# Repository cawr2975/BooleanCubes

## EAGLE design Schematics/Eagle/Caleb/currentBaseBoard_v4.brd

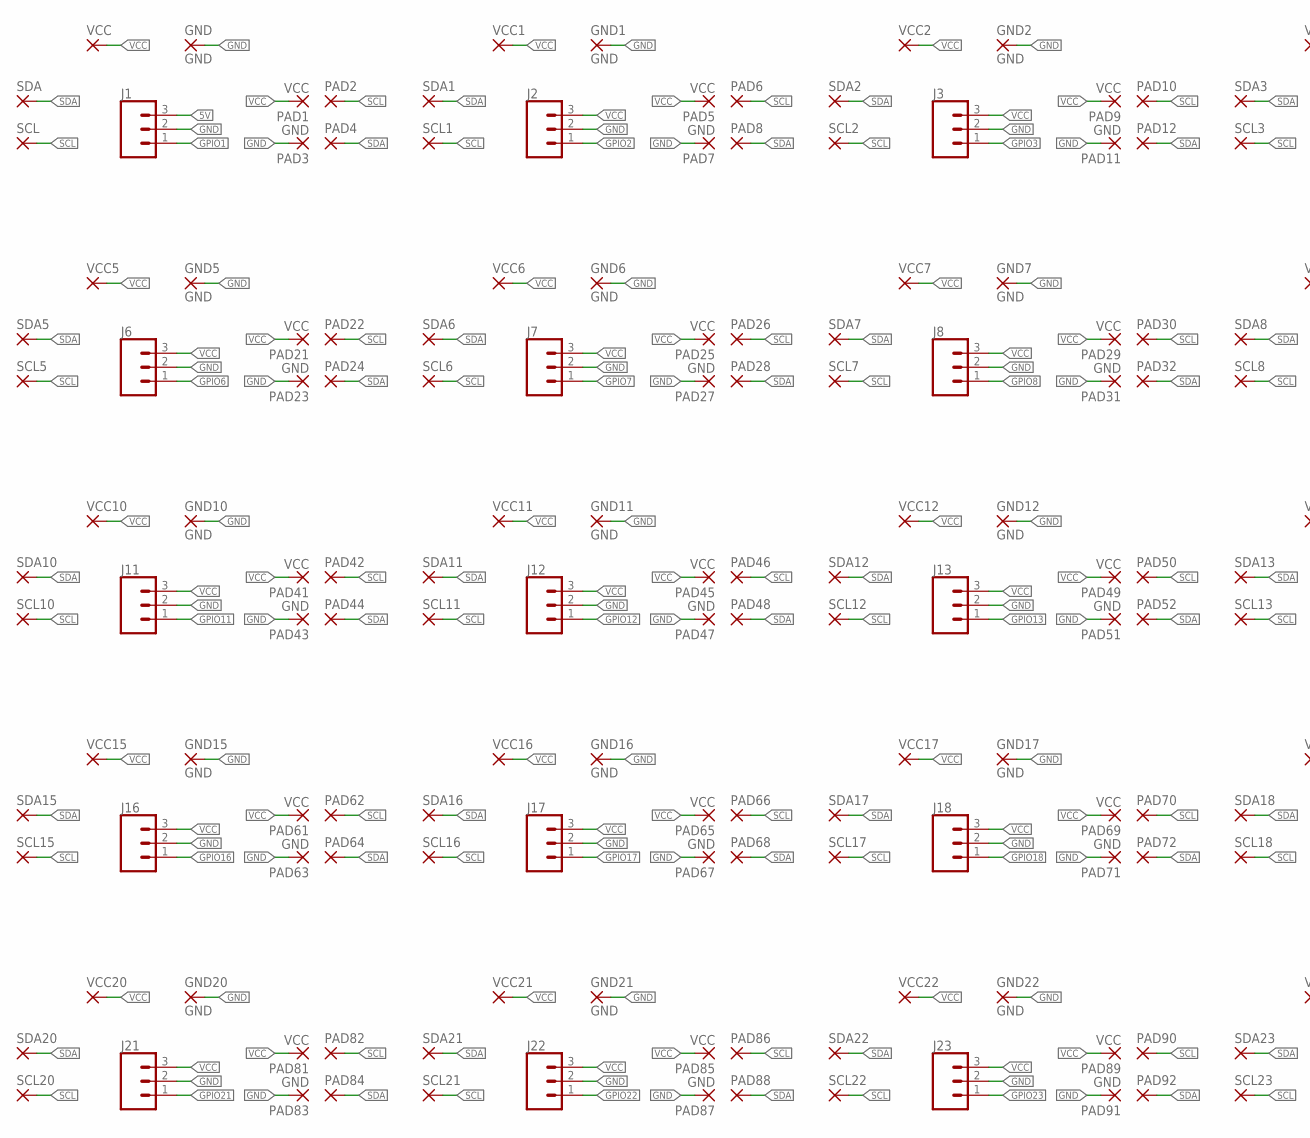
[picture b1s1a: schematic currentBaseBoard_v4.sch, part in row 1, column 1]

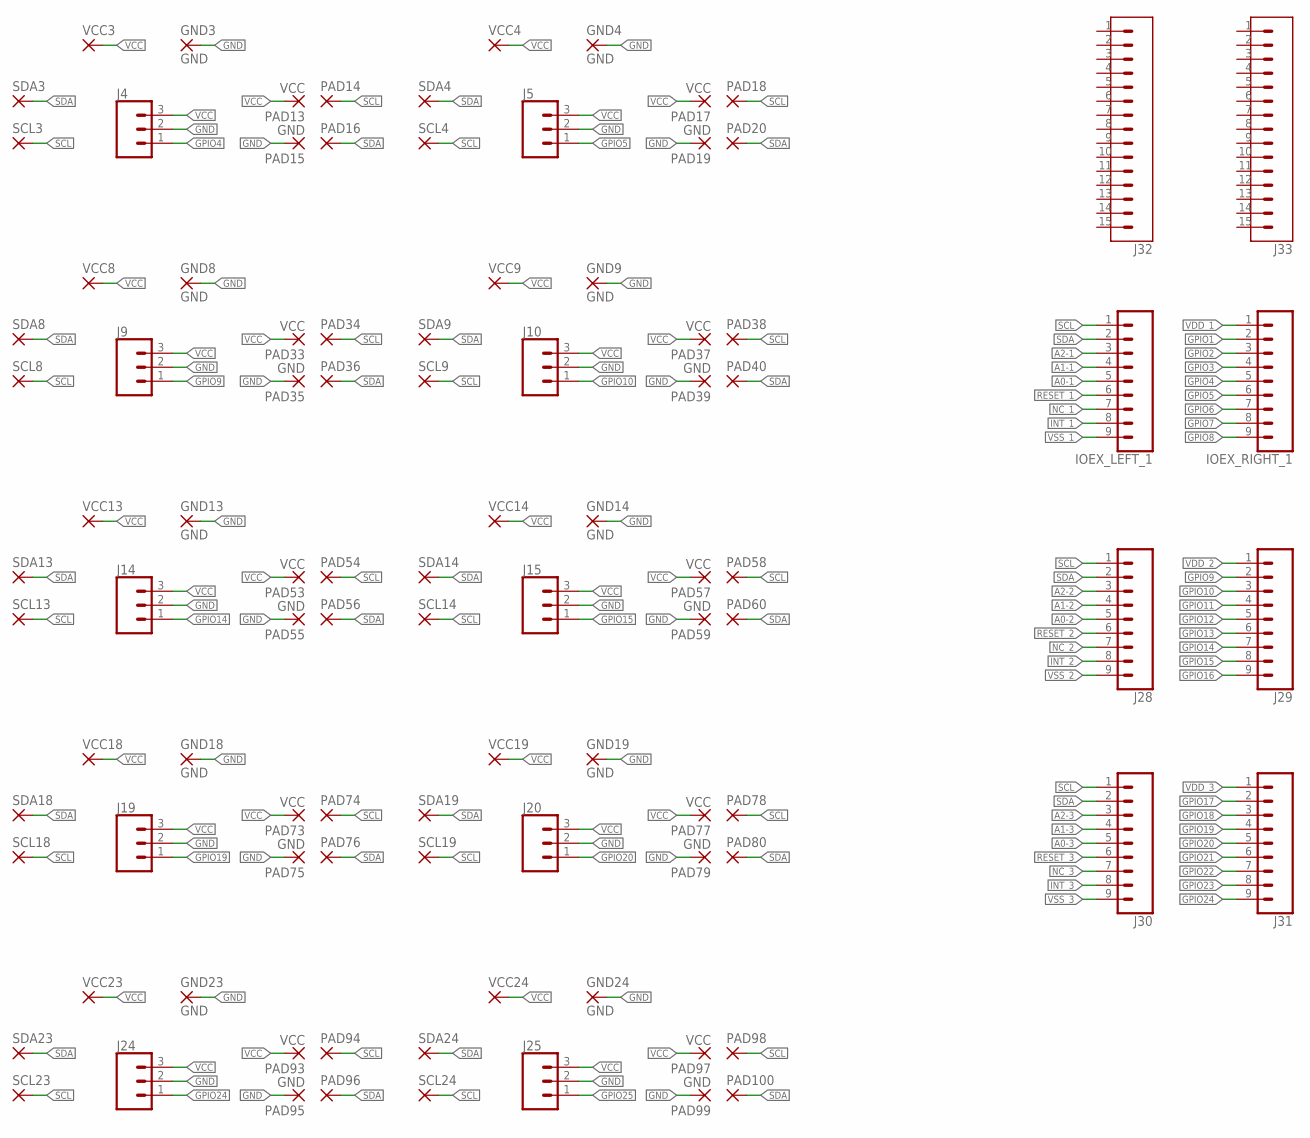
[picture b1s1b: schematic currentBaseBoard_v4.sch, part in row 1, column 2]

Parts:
GND, GND1, GND2, GND3, GND4, GND5, GND6, GND7, GND8, GND9, GND10, GND11, GND12, GND13, GND14, GND15, GND16, GND17, GND18, GND19, GND20, GND21, GND22, GND23, GND24: GND; 2,15/1,0
IOEX_LEFT_1: CONN_09; 1X09
IOEX_RIGHT_1: CONN_09; 1X09
J1, J2, J3, J4, J5, J6, J7, J8, J9, J10, J11, J12, J13, J14, J15, J16, J17, J18, J19, J20, J21, J22, J23, J24, J25: CONN_03; 1X03
J28, J29, J30, J31: CONN_09; 1X09
J32, J33: CONN_06SMD_MALE; 1X15_SMD_MALE
PAD1, PAD5, PAD9, PAD13, PAD17, PAD21, PAD25, PAD29, PAD33, PAD37, PAD41, PAD45, PAD49, PAD53, PAD57, PAD61, PAD65, PAD69, PAD73, PAD77, PAD81, PAD85, PAD89, PAD93, PAD97: VCC; 2,15/1,0
PAD2, PAD4, PAD6, PAD8, PAD10, PAD12, PAD14, PAD16, PAD18, PAD20, PAD22, PAD24, PAD26, PAD28, PAD30, PAD32, PAD34, PAD36, PAD38, PAD40, PAD42, PAD44, PAD46, PAD48, PAD50, PAD52, PAD54, PAD56, PAD58, PAD60, PAD62, PAD64, PAD66, PAD68, PAD70, PAD72, PAD74, PAD76, PAD78, PAD80, PAD82, PAD84, PAD86, PAD88, PAD90, PAD92, PAD94, PAD96, PAD98, PAD100: 2,15/1,0
PAD3, PAD7, PAD11, PAD15, PAD19, PAD23, PAD27, PAD31, PAD35, PAD39, PAD43, PAD47, PAD51, PAD55, PAD59, PAD63, PAD67, PAD71, PAD75, PAD79, PAD83, PAD87, PAD91, PAD95, PAD99: GND; 2,15/1,0
SCL, SCL1, SCL2, SCL3, SCL4, SCL5, SCL6, SCL7, SCL8, SCL9, SCL10, SCL11, SCL12, SCL13, SCL14, SCL15, SCL16, SCL17, SCL18, SCL19, SCL20, SCL21, SCL22, SCL23, SCL24: 2,15/1,0
SDA, SDA1, SDA2, SDA3, SDA4, SDA5, SDA6, SDA7, SDA8, SDA9, SDA10, SDA11, SDA12, SDA13, SDA14, SDA15, SDA16, SDA17, SDA18, SDA19, SDA20, SDA21, SDA22, SDA23, SDA24: 2,15/1,0
VCC, VCC1, VCC2, VCC3, VCC4, VCC5, VCC6, VCC7, VCC8, VCC9, VCC10, VCC11, VCC12, VCC13, VCC14, VCC15, VCC16, VCC17, VCC18, VCC19, VCC20, VCC21, VCC22, VCC23, VCC24: 2,15/1,0

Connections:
5V: J1.3
A0-1: IOEX_LEFT_1.5
A0-2: J28.5
A0-3: J30.5
A1-1: IOEX_LEFT_1.4
A1-2: J28.4
A1-3: J30.4
A2-1: IOEX_LEFT_1.3
A2-2: J28.3
A2-3: J30.3
GND: GND.1, GND1.1, GND2.1, GND3.1, GND4.1, GND5.1, GND6.1, GND7.1, GND8.1, GND9.1, GND10.1, GND11.1, GND12.1, GND13.1, GND14.1, GND15.1, GND16.1, GND17.1, GND18.1, GND19.1, GND20.1, GND21.1, GND22.1, GND23.1, GND24.1, J1.2, J2.2, J3.2, J4.2, J5.2, J6.2, J7.2, J8.2, J9.2, J10.2, J11.2, J12.2, J13.2, J14.2, J15.2, J16.2, J17.2, J18.2, J19.2, J20.2, J21.2, J22.2, J23.2, J24.2, J25.2, PAD3.1, PAD7.1, PAD11.1, PAD15.1, PAD19.1, PAD23.1, PAD27.1, PAD31.1, PAD35.1, PAD39.1, PAD43.1, PAD47.1, PAD51.1, PAD55.1, PAD59.1, PAD63.1, PAD67.1, PAD71.1, PAD75.1, PAD79.1, PAD83.1, PAD87.1, PAD91.1, PAD95.1, PAD99.1
GPIO1: IOEX_RIGHT_1.2, J1.1
GPIO2: IOEX_RIGHT_1.3, J2.1
GPIO3: IOEX_RIGHT_1.4, J3.1
GPIO4: IOEX_RIGHT_1.5, J4.1
GPIO5: IOEX_RIGHT_1.6, J5.1
GPIO6: IOEX_RIGHT_1.7, J6.1
GPIO7: IOEX_RIGHT_1.8, J7.1
GPIO8: IOEX_RIGHT_1.9, J8.1
GPIO9: J9.1, J29.2
GPIO10: J10.1, J29.3
GPIO11: J11.1, J29.4
GPIO12: J12.1, J29.5
GPIO13: J13.1, J29.6
GPIO14: J14.1, J29.7
GPIO15: J15.1, J29.8
GPIO16: J16.1, J29.9
GPIO17: J17.1, J31.2
GPIO18: J18.1, J31.3
GPIO19: J19.1, J31.4
GPIO20: J20.1, J31.5
GPIO21: J21.1, J31.6
GPIO22: J22.1, J31.7
GPIO23: J23.1, J31.8
GPIO24: J24.1, J31.9
GPIO25: J25.1
INT_1: IOEX_LEFT_1.8
INT_2: J28.8
INT_3: J30.8
NC_1: IOEX_LEFT_1.7
NC_2: J28.7
NC_3: J30.7
RESET_1: IOEX_LEFT_1.6
RESET_2: J28.6
RESET_3: J30.6
SCL: IOEX_LEFT_1.1, J28.1, J30.1, PAD2.1, PAD6.1, PAD10.1, PAD14.1, PAD18.1, PAD22.1, PAD26.1, PAD30.1, PAD34.1, PAD38.1, PAD42.1, PAD46.1, PAD50.1, PAD54.1, PAD58.1, PAD62.1, PAD66.1, PAD70.1, PAD74.1, PAD78.1, PAD82.1, PAD86.1, PAD90.1, PAD94.1, PAD98.1, SCL.1, SCL1.1, SCL2.1, SCL3.1, SCL4.1, SCL5.1, SCL6.1, SCL7.1, SCL8.1, SCL9.1, SCL10.1, SCL11.1, SCL12.1, SCL13.1, SCL14.1, SCL15.1, SCL16.1, SCL17.1, SCL18.1, SCL19.1, SCL20.1, SCL21.1, SCL22.1, SCL23.1, SCL24.1
SDA: IOEX_LEFT_1.2, J28.2, J30.2, PAD4.1, PAD8.1, PAD12.1, PAD16.1, PAD20.1, PAD24.1, PAD28.1, PAD32.1, PAD36.1, PAD40.1, PAD44.1, PAD48.1, PAD52.1, PAD56.1, PAD60.1, PAD64.1, PAD68.1, PAD72.1, PAD76.1, PAD80.1, PAD84.1, PAD88.1, PAD92.1, PAD96.1, PAD100.1, SDA.1, SDA1.1, SDA2.1, SDA3.1, SDA4.1, SDA5.1, SDA6.1, SDA7.1, SDA8.1, SDA9.1, SDA10.1, SDA11.1, SDA12.1, SDA13.1, SDA14.1, SDA15.1, SDA16.1, SDA17.1, SDA18.1, SDA19.1, SDA20.1, SDA21.1, SDA22.1, SDA23.1, SDA24.1
VCC: J2.3, J3.3, J4.3, J5.3, J6.3, J7.3, J8.3, J9.3, J10.3, J11.3, J12.3, J13.3, J14.3, J15.3, J16.3, J17.3, J18.3, J19.3, J20.3, J21.3, J22.3, J23.3, J24.3, J25.3, PAD1.1, PAD5.1, PAD9.1, PAD13.1, PAD17.1, PAD21.1, PAD25.1, PAD29.1, PAD33.1, PAD37.1, PAD41.1, PAD45.1, PAD49.1, PAD53.1, PAD57.1, PAD61.1, PAD65.1, PAD69.1, PAD73.1, PAD77.1, PAD81.1, PAD85.1, PAD89.1, PAD93.1, PAD97.1, VCC.1, VCC1.1, VCC2.1, VCC3.1, VCC4.1, VCC5.1, VCC6.1, VCC7.1, VCC8.1, VCC9.1, VCC10.1, VCC11.1, VCC12.1, VCC13.1, VCC14.1, VCC15.1, VCC16.1, VCC17.1, VCC18.1, VCC19.1, VCC20.1, VCC21.1, VCC22.1, VCC23.1, VCC24.1
VDD_1: IOEX_RIGHT_1.1
VDD_2: J29.1
VDD_3: J31.1
VSS_1: IOEX_LEFT_1.9
VSS_2: J28.9
VSS_3: J30.9

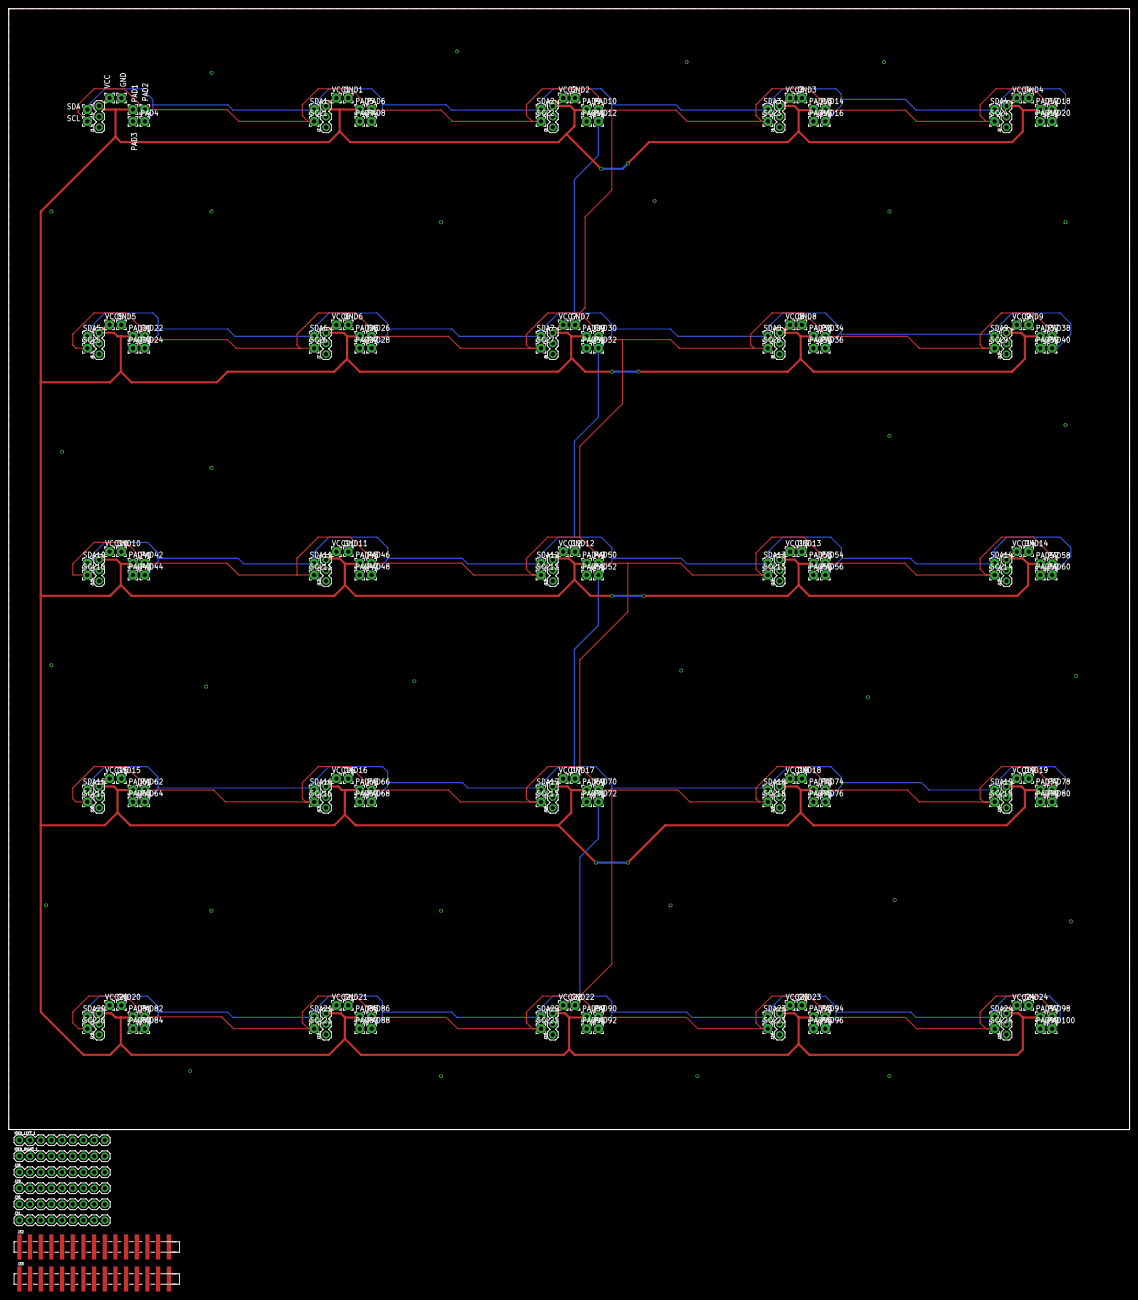
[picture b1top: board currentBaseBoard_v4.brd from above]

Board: 2 copper layers, 266.7 x 266.7 mm, 233 parts (0 on the bottom side), 28 nets.

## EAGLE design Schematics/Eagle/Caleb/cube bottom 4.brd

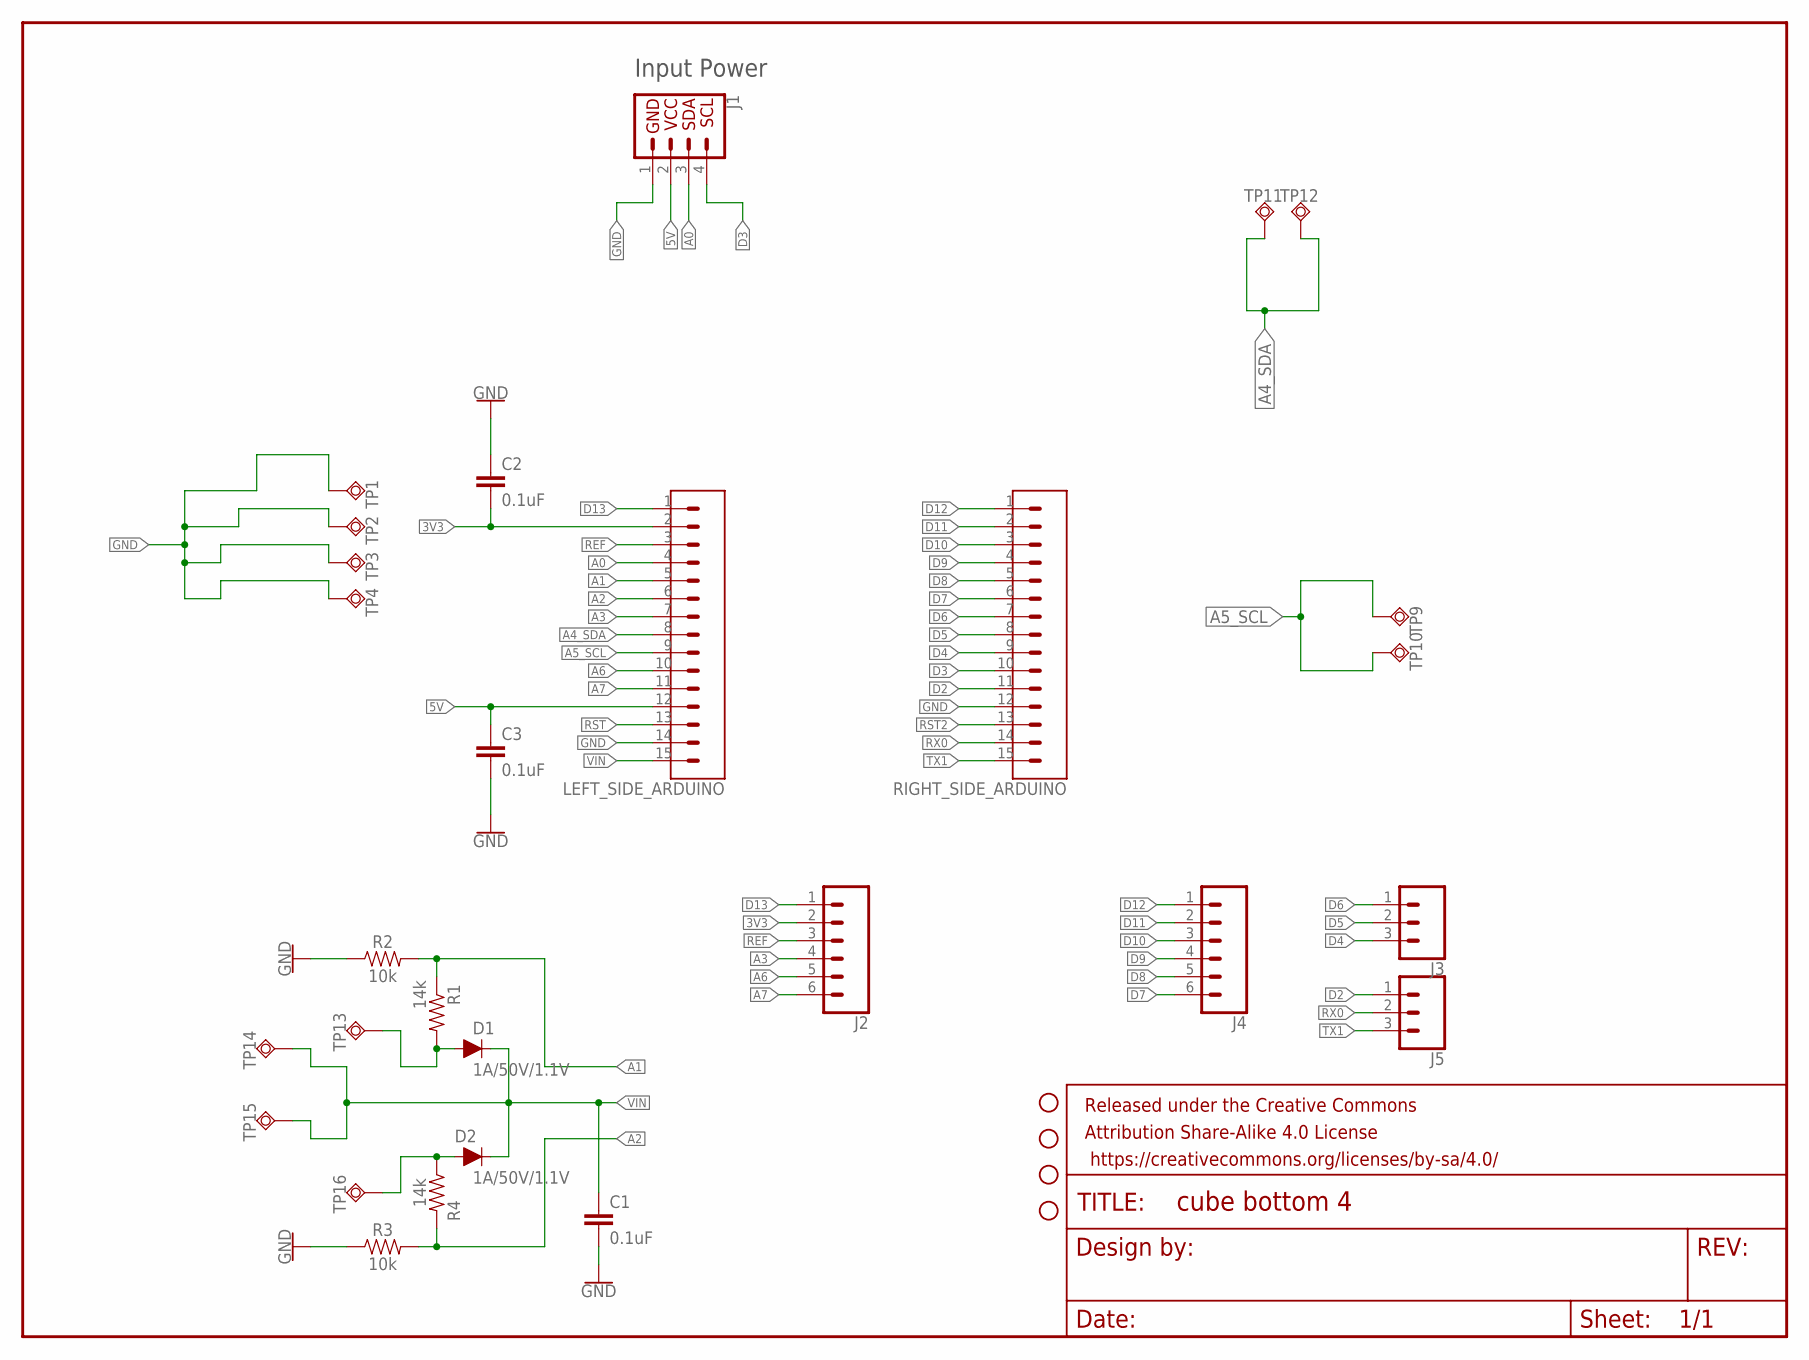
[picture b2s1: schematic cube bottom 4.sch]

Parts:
C1, C2, C3: 0.1uF; 0603
D1, D2: 1A/50V/1.1V; DIODE-1N4001
FRAME1: FRAME-LETTERNO_PACKAGE; DUMMY
H1, H2, H3, H4: STAND-OFF
J1: QWIIC_CONNECTORJS-1MM; 1X04_1MM_RA
J2, J4: CONN_06SILK_FEMALE_PTH; 1X06
J3, J5: CONN_03; 1X03
LEFT_SIDE_ARDUINO: CONN_06SMD_MALE; 1X15_SMD_MALE
R1, R4: 14k; 0603
R2, R3: 10k; 0603
RIGHT_SIDE_ARDUINO: CONN_06SMD_MALE; 1X15_SMD_MALE
TP1, TP2, TP3, TP4, TP9, TP10, TP11, TP12, TP13, TP14, TP15, TP16: TPSQTP20SQ; TP20SQ

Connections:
3V3: C2.2, J2.2, LEFT_SIDE_ARDUINO.2
5V: C3.1, J1.2 (VCC), LEFT_SIDE_ARDUINO.12
A0: J1.3 (SDA), LEFT_SIDE_ARDUINO.4
A1: LEFT_SIDE_ARDUINO.5, R1.1, R2.2
A2: LEFT_SIDE_ARDUINO.6, R3.2, R4.2
A3: J2.4, LEFT_SIDE_ARDUINO.7
A4_SDA: LEFT_SIDE_ARDUINO.8, TP11.TP, TP12.TP
A5_SCL: LEFT_SIDE_ARDUINO.9, TP9.TP, TP10.TP
A6: J2.5, LEFT_SIDE_ARDUINO.10
A7: J2.6, LEFT_SIDE_ARDUINO.11
D2: J5.1, RIGHT_SIDE_ARDUINO.11
D3: J1.4 (SCL), RIGHT_SIDE_ARDUINO.10
D4: J3.3, RIGHT_SIDE_ARDUINO.9
D5: J3.2, RIGHT_SIDE_ARDUINO.8
D6: J3.1, RIGHT_SIDE_ARDUINO.7
D7: J4.6, RIGHT_SIDE_ARDUINO.6
D8: J4.5, RIGHT_SIDE_ARDUINO.5
D9: J4.4, RIGHT_SIDE_ARDUINO.4
D10: J4.3, RIGHT_SIDE_ARDUINO.3
D11: J4.2, RIGHT_SIDE_ARDUINO.2
D12: J4.1, RIGHT_SIDE_ARDUINO.1
D13: J2.1, LEFT_SIDE_ARDUINO.1
DTP1: D2.A, R4.1, TP16.TP
DTP2: D1.A, R1.2, TP13.TP
GND: C1.2, C2.1, C3.2, J1.1 (GND), LEFT_SIDE_ARDUINO.14, R2.1, R3.1, RIGHT_SIDE_ARDUINO.12, TP1.TP, TP2.TP, TP3.TP, TP4.TP
REF: J2.3, LEFT_SIDE_ARDUINO.3
RST: LEFT_SIDE_ARDUINO.13
RST2: RIGHT_SIDE_ARDUINO.13
RX0: J5.2, RIGHT_SIDE_ARDUINO.14
TX1: J5.3, RIGHT_SIDE_ARDUINO.15
VIN: C1.1, D1.C, D2.C, LEFT_SIDE_ARDUINO.15, TP14.TP, TP15.TP

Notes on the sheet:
Input Power

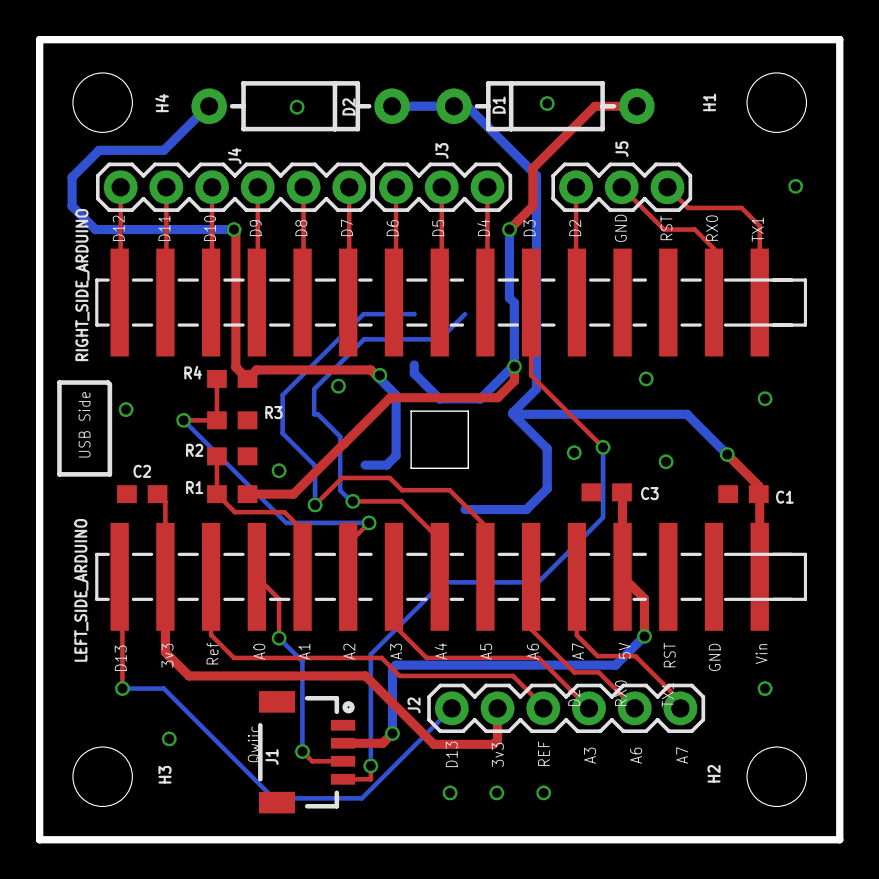
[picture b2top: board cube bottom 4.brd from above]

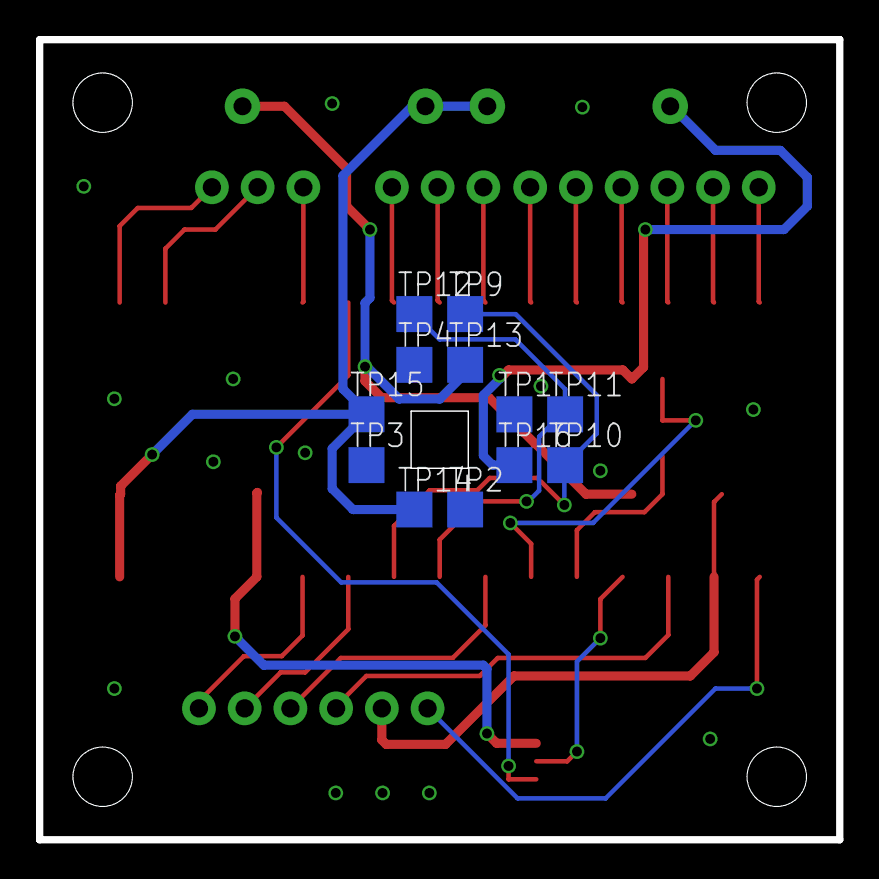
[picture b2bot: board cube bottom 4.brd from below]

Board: 2 copper layers, 44.5 x 44.5 mm, 33 parts (12 on the bottom side), 29 nets.

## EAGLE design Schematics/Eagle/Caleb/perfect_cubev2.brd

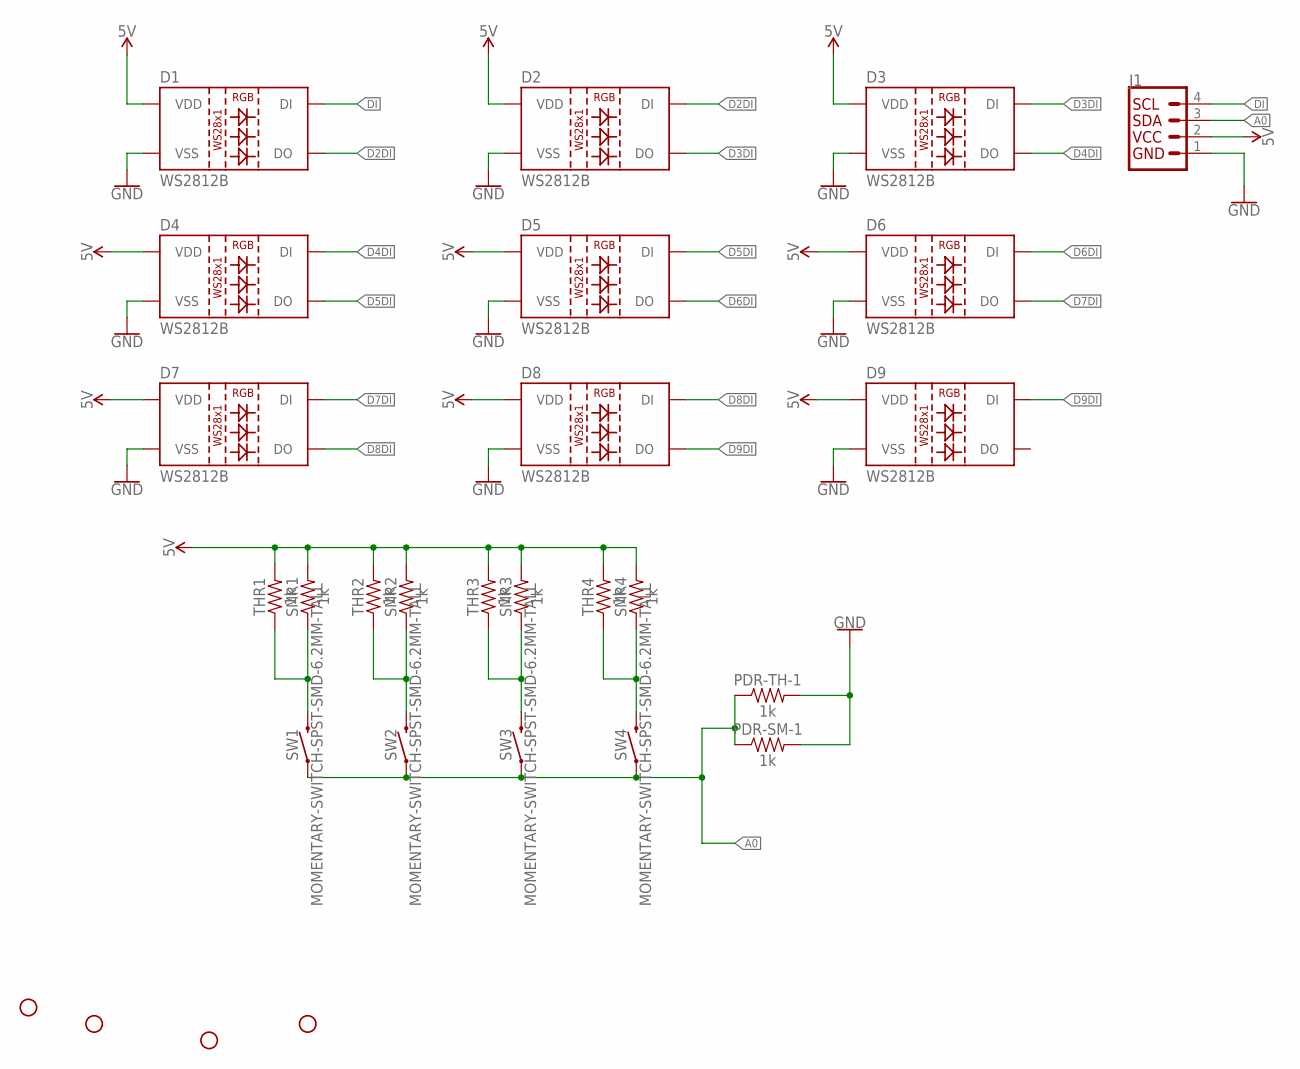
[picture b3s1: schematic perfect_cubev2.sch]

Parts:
D1, D2, D3, D4, D5, D6, D7, D8, D9: WS2812B
H1, H2, H3, H4: STAND-OFF
J1: QWIIC_CONNECTORJS-1MM; 1X04_1MM_RA
PDR-SM-1: 1k; 0603
PDR-TH-1: 1k; AXIAL-0.3
SMR1, SMR2, SMR3, SMR4: 1k; 0603
SW1, SW2, SW3, SW4: MOMENTARY-SWITCH-SPST-SMD-6.2MM-TALL; TACTILE_SWITCH_SMD_6.2MM_TALL
THR1, THR2, THR3, THR4: 1k; AXIAL-0.3

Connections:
5V: D1.1 (VDD), D2.1 (VDD), D3.1 (VDD), D4.1 (VDD), D5.1 (VDD), D6.1 (VDD), D7.1 (VDD), D8.1 (VDD), D9.1 (VDD), J1.2 (VCC), SMR1.2, SMR2.2, SMR3.2, SMR4.2, THR1.P$2 (2), THR2.P$2 (2), THR3.P$2 (2), THR4.P$2 (2)
A0: J1.3 (SDA), PDR-SM-1.1, PDR-TH-1.P$1 (1), SW1.A2 (1), SW2.A2 (1), SW3.A2 (1), SW4.A2 (1)
D2DI: D1.2 (DO), D2.4 (DI)
D3DI: D2.2 (DO), D3.4 (DI)
D4DI: D3.2 (DO), D4.4 (DI)
D5DI: D4.2 (DO), D5.4 (DI)
D6DI: D5.2 (DO), D6.4 (DI)
D7DI: D6.2 (DO), D7.4 (DI)
D8DI: D7.2 (DO), D8.4 (DI)
D9DI: D8.2 (DO), D9.4 (DI)
DI: D1.4 (DI), J1.4 (SCL)
GND: D1.3 (VSS), D2.3 (VSS), D3.3 (VSS), D4.3 (VSS), D5.3 (VSS), D6.3 (VSS), D7.3 (VSS), D8.3 (VSS), D9.3 (VSS), J1.1 (GND), PDR-SM-1.2, PDR-TH-1.P$2 (2)
unnamed: SMR1.1, SW1.B2 (2), THR1.P$1 (1)
unnamed: SMR2.1, SW2.B2 (2), THR2.P$1 (1)
unnamed: SMR3.1, SW3.B2 (2), THR3.P$1 (1)
unnamed: SMR4.1, SW4.B2 (2), THR4.P$1 (1)

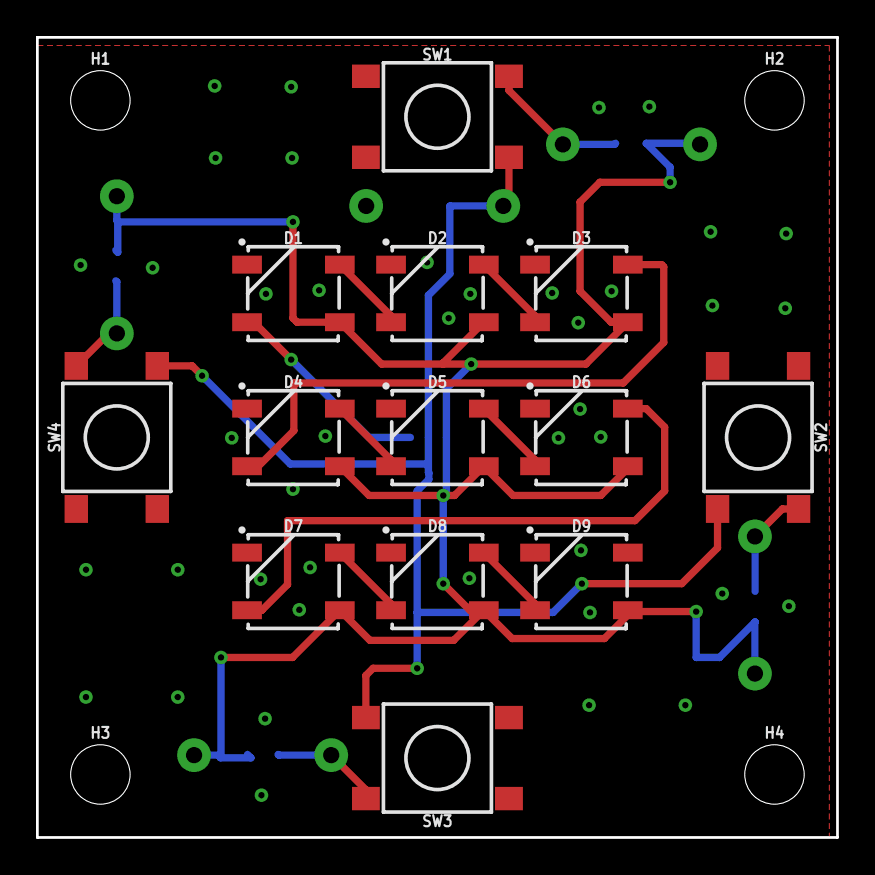
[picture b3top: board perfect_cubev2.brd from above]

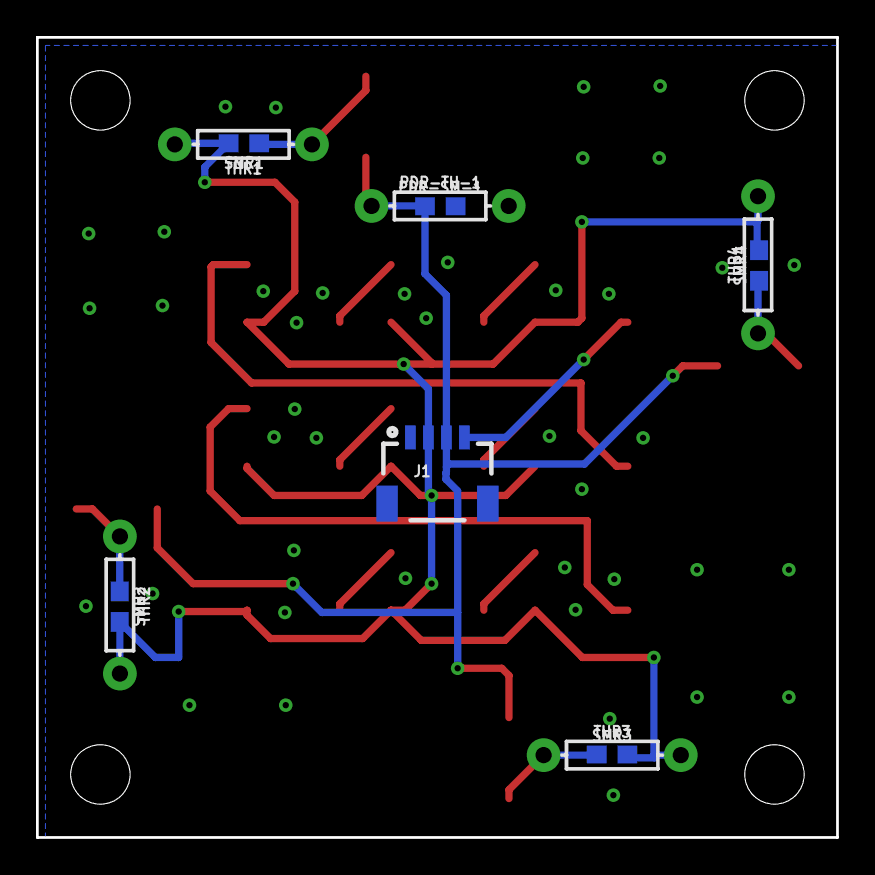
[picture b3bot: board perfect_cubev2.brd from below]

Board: 2 copper layers, 44.5 x 44.5 mm, 28 parts (11 on the bottom side), 16 nets.

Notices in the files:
parts and their libraries:
SparkFun-Aesthetics: Licensing: Creative Commons ShareAlike 4.0 International - https://creativecommons.org/licenses/by-sa/4.0
SparkFun-Aesthetics: Released under the Creative Commons Attribution Share-Alike 4.0 License
SparkFun-Aesthetics: https://creativecommons.org/licenses/by-sa/4.0
